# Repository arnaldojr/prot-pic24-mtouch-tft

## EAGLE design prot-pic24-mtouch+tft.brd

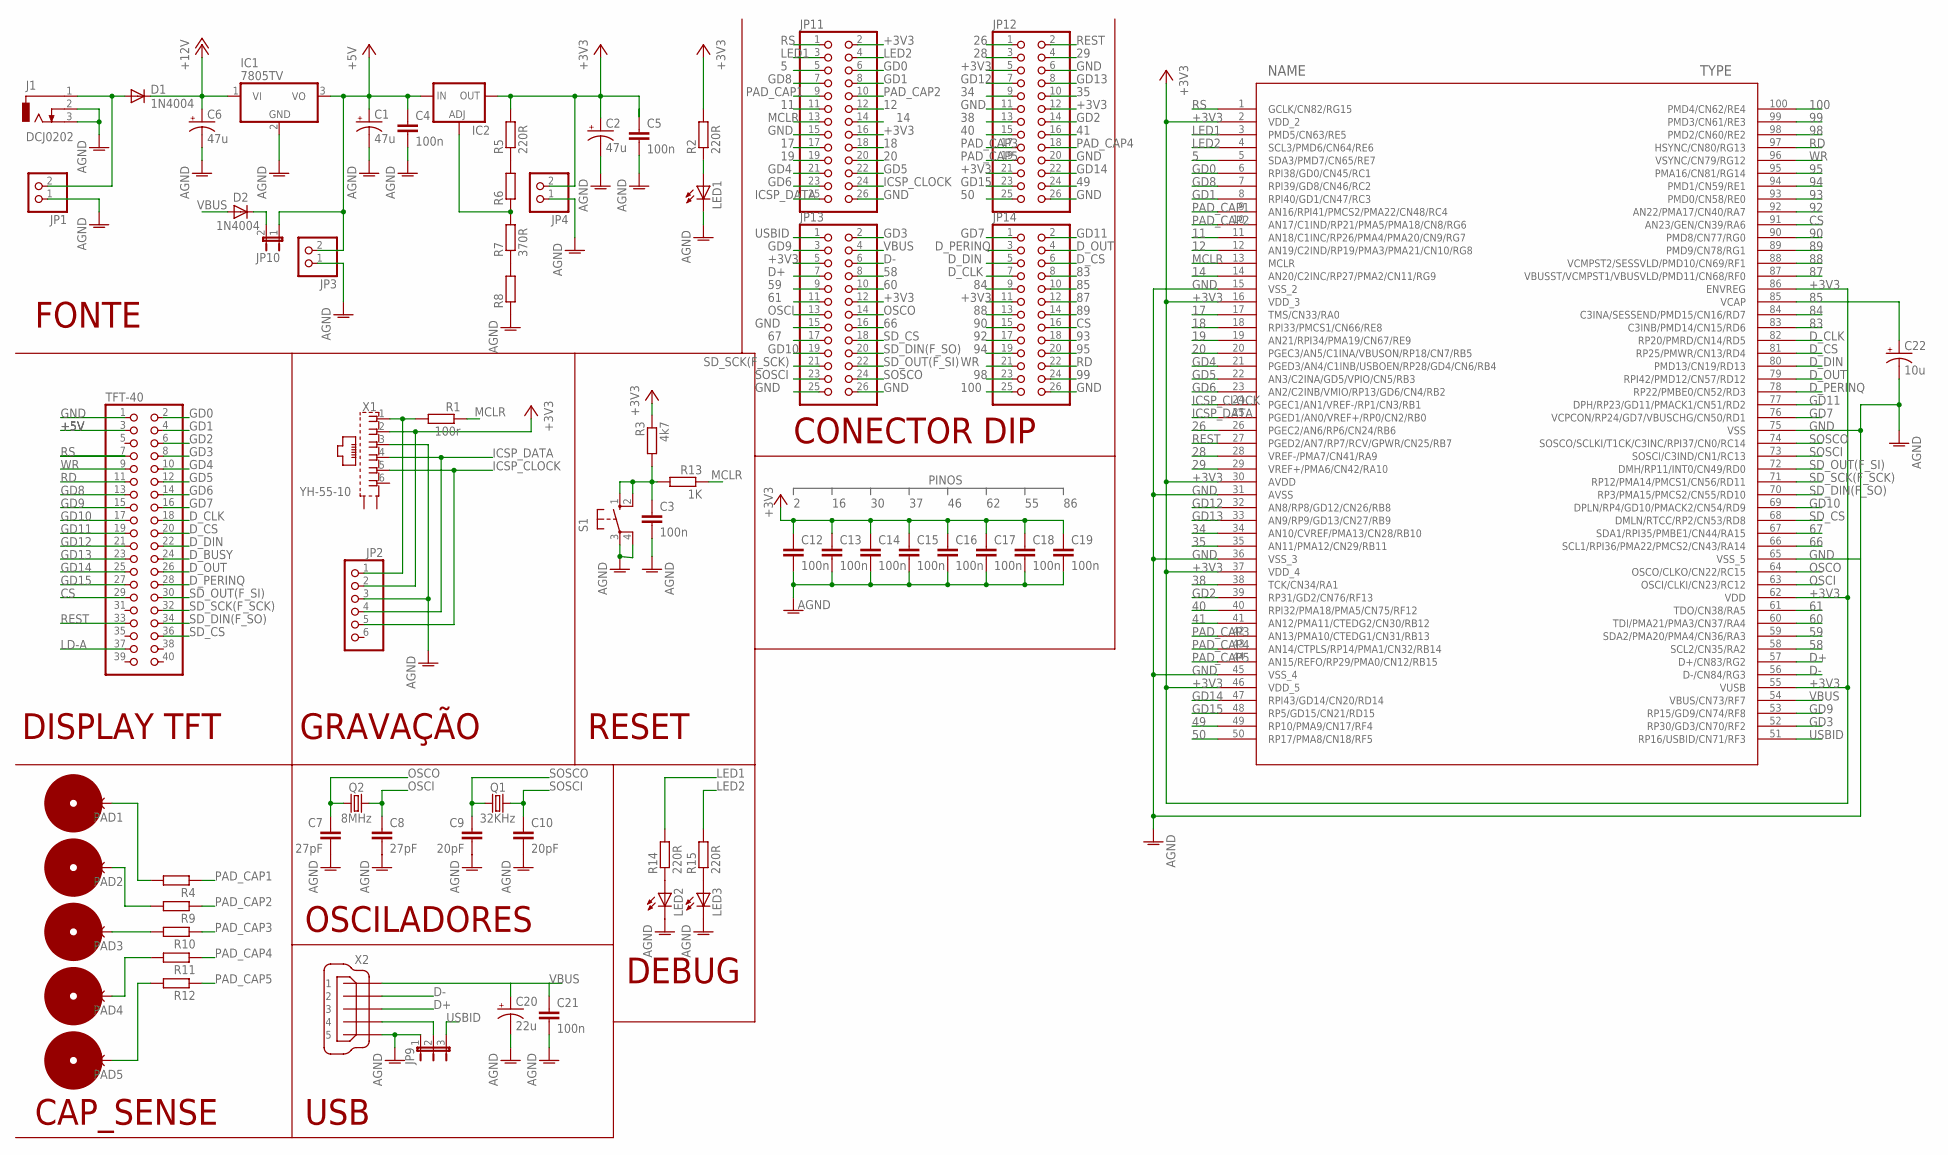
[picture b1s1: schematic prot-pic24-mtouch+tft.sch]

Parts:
C1, C2, C6: 47u; E2,5-5
C3, C4, C5: 100n; C050-025X075
C7, C8: 27pF; C025-030X050
C9, C10: 20pF; C025-030X050
C12: 100n; C025-025X050
C13, C14, C15, C16, C17, C18, C19, C21: 100n; C025-030X050
C20: 22u; E2,5-5
C22: 10u; E2,5-5
D1, D2: 1N4004; DO41-10
IC1: 7805TV; TO220V
IC2: LM317TS; 317TS
J1: DCJ0202
JP1, JP3, JP4: PINHD-1X2; 1X02
JP2: PINHD-1X6; 1X06
JP9: JP2E; JP2
JP10: JP1E; JP1
JP11, JP12, JP13, JP14: PINHD-2X13; 2X13
LED1, LED2, LED3: LED3MM
PAD1, PAD2, PAD3, PAD4, PAD5: SMD5; SMD2,54-5,08
Q1: 32KHz; TC26V
Q2: 8MHz; HC49/S
R1: 100r; 0204V
R2, R4, R5, R9, R10, R11, R12, R14, R15: 220R; 0204V
R3: 4k7; 0204V
R6, R8: R-EU_0204/2V; 0204V
R7: 370R; 0204V
R13: 1K; 0204V
S1: 10-XX; B3F-10XX
TFT-40: PINHD-2X20; 2X20
U$1: PIC24FJXXXDAX10_; TQFP100_12X12MC
X1: YH-55-10
X2: MINI-USB-32005-301; 32005-301

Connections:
5: JP11.5, U$1.5 (SDA3/PMD7/CN65/RE7)
11: JP11.11, U$1.11 (AN18/C1INC/RP26/PMA4/PMA20/CN9/RG7)
12: JP11.12, U$1.12 (AN19/C2IND/RP19/PMA3/PMA21/CN10/RG8)
14: JP11.14, U$1.14 (AN20/C2INC/RP27/PMA2/CN11/RG9)
17: JP11.17, U$1.17 (TMS/CN33/RA0)
18: JP11.18, U$1.18 (RPI33/PMCS1/CN66/RE8)
19: JP11.19, U$1.19 (AN21/RPI34/PMA19/CN67/RE9)
20: JP11.20, U$1.20 (PGEC3/AN5/C1INA/VBUSON/RP18/CN7/RB5)
26: JP12.1, U$1.26 (PGEC2/AN6/RP6/CN24/RB6)
28: JP12.3, U$1.28 (VREF-/PMA7/CN41/RA9)
29: JP12.4, U$1.29 (VREF+/PMA6/CN42/RA10)
34: JP12.9, U$1.34 (AN10/CVREF/PMA13/CN28/RB10)
35: JP12.10, U$1.35 (AN11/PMA12/CN29/RB11)
38: JP12.13, U$1.38 (TCK/CN34/RA1)
40: JP12.15, U$1.40 (RPI32/PMA18/PMA5/CN75/RF12)
41: JP12.16, U$1.41 (AN12/PMA11/CTEDG2/CN30/RB12)
49: JP12.24, U$1.49 (RP10/PMA9/CN17/RF4)
50: JP12.25, U$1.50 (RP17/PMA8/CN18/RF5)
58: JP13.8, U$1.58 (SCL2/CN35/RA2)
59: JP13.9, U$1.59 (SDA2/PMA20/PMA4/CN36/RA3)
60: JP13.10, U$1.60 (TDI/PMA21/PMA3/CN37/RA4)
61: JP13.11, U$1.61 (TDO/CN38/RA5)
66: JP13.16, U$1.66 (SCL1/RPI36/PMA22/PMCS2/CN43/RA14)
67: JP13.17, U$1.67 (SDA1/RPI35/PMBE1/CN44/RA15)
83: JP14.8, U$1.83 (C3INB/PMD14/CN15/RD6)
84: JP14.9, U$1.84 (C3INA/SESSEND/PMD15/CN16/RD7)
85: C22.+, JP14.10, U$1.85 (VCAP)
87: JP14.12, U$1.87 (VBUSST/VCMPST1/VBUSVLD/PMD11/CN68/RF0)
88: JP14.13, U$1.88 (VCMPST2/SESSVLD/PMD10/CN69/RF1)
89: JP14.14, U$1.89 (PMD9/CN78/RG1)
90: JP14.15, U$1.90 (PMD8/CN77/RG0)
92: JP14.17, U$1.92 (AN22/PMA17/CN40/RA7)
93: JP14.18, U$1.93 (PMD0/CN58/RE0)
94: JP14.19, U$1.94 (PMD1/CN59/RE1)
95: JP14.20, U$1.95 (PMA16/CN81/RG14)
98: JP14.23, U$1.98 (PMD2/CN60/RE2)
99: JP14.24, U$1.99 (PMD3/CN61/RE3)
100: JP14.25, U$1.100 (PMD4/CN62/RE4)
+3V3: C2.+, C5.1, C12.1, C13.1, C14.1, C15.1, C16.1, C17.1, C18.1, C19.1, IC2.2 (OUT), JP2.2, JP4.2, JP11.2, JP11.16, JP12.5, JP12.12, JP12.21, JP13.5, JP13.12, JP14.11, R2.2, R3.1, R5.2, U$1.2 (VDD_2), U$1.16 (VDD_3), U$1.30 (AVDD), U$1.37 (VDD_4), U$1.46 (VDD_5), U$1.55 (VUSB), U$1.62 (VDD), U$1.86 (ENVREG), X1.2
+5V: C1.+, C4.1, IC1.3 (VO), IC2.3 (IN), JP3.2, JP10.1, TFT-40.3
+12V: C6.+, D1.C, IC1.1 (VI)
AGND: LED2.K (C), LED3.K (C)
CS: JP14.16, TFT-40.29, U$1.91 (AN23/GEN/CN39/RA6)
D+: JP13.7, U$1.57 (D+/CN83/RG2), X2.3
D-: JP13.6, U$1.56 (D-/CN84/RG3), X2.2
D_BUSY: TFT-40.24
D_CLK: JP14.7, TFT-40.18, U$1.82 (RP20/PMRD/CN14/RD5)
D_CS: JP14.6, TFT-40.20, U$1.81 (RP25/PMWR/CN13/RD4)
D_DIN: JP14.5, TFT-40.22, U$1.80 (PMD13/CN19/RD13)
D_OUT: JP14.4, TFT-40.26, U$1.79 (RPI42/PMD12/CN57/RD12)
D_PERINQ: JP14.3, TFT-40.28, U$1.78 (RP22/PMBE0/CN52/RD3)
GD0: JP11.6, TFT-40.2, U$1.6 (RPI38/GD0/CN45/RC1)
GD1: JP11.8, TFT-40.4, U$1.8 (RPI40/GD1/CN47/RC3)
GD2: JP12.14, TFT-40.6, U$1.39 (RP31/GD2/CN76/RF13)
GD3: JP13.2, TFT-40.8, U$1.52 (RP30/GD3/CN70/RF2)
GD4: JP11.21, TFT-40.10, U$1.21 (PGED3/AN4/C1INB/USBOEN/RP28/GD4/CN6/RB4)
GD5: JP11.22, TFT-40.12, U$1.22 (AN3/C2INA/GD5/VPIO/CN5/RB3)
GD6: JP11.23, TFT-40.14, U$1.23 (AN2/C2INB/VMIO/RP13/GD6/CN4/RB2)
GD7: JP14.1, TFT-40.16, U$1.76 (VCPCON/RP24/GD7/VBUSCHG/CN50/RD1)
GD8: JP11.7, TFT-40.13, U$1.7 (RPI39/GD8/CN46/RC2)
GD9: JP13.3, TFT-40.15, U$1.53 (RP15/GD9/CN74/RF8)
GD10: JP13.19, TFT-40.17, U$1.69 (DPLN/RP4/GD10/PMACK2/CN54/RD9)
GD11: JP14.2, TFT-40.19, U$1.77 (DPH/RP23/GD11/PMACK1/CN51/RD2)
GD12: JP12.7, TFT-40.21, U$1.32 (AN8/RP8/GD12/CN26/RB8)
GD13: JP12.8, TFT-40.23, U$1.33 (AN9/RP9/GD13/CN27/RB9)
GD14: JP12.22, TFT-40.25, U$1.47 (RPI43/GD14/CN20/RD14)
GD15: JP12.23, TFT-40.27, U$1.48 (RP5/GD15/CN21/RD15)
GND: C1.-, C2.-, C3.2, C4.2, C5.2, C6.-, C7.2, C8.2, C9.2, C10.2, C12.2, C13.2, C14.2, C15.2, C16.2, C17.2, C18.2, C19.2, C20.-, C21.2, C22.-, IC1.2 (GND), J1.2, J1.3, JP1.1, JP2.3, JP3.1, JP4.1, JP9.1, JP11.15, JP11.26, JP12.6, JP12.11, JP12.20, JP12.26, JP13.15, JP13.25, JP13.26, JP14.26, LED1.K (C), R8.1, S1.3, S1.4 (P1), TFT-40.1, U$1.15 (VSS_2), U$1.31 (AVSS), U$1.36 (VSS_3), U$1.45 (VSS_4), U$1.65 (VSS_5), U$1.75 (VSS), X1.3, X2.5
ICSP_CLOCK: JP2.5, JP11.24, U$1.24 (PGEC1/AN1/VREF-/RP1/CN3/RB1), X1.5
ICSP_DATA: JP2.4, JP11.25, U$1.25 (PGED1/AN0/VREF+/RP0/CN2/RB0), X1.4
LD-A: TFT-40.37
LED1: JP11.3, R14.2, U$1.3 (PMD5/CN63/RE5)
LED2: JP11.4, R15.2, U$1.4 (SCL3/PMD6/CN64/RE6)
MCLR: JP11.13, R1.1, R13.1, U$1.13 (MCLR)
unnamed: D1.A, J1.1, JP1.2
unnamed: LED1.A, R2.1
unnamed: JP2.1, R1.2, X1.1
unnamed: R5.1, R6.2
unnamed: IC2.1 (ADJ), R6.1, R7.2
unnamed: R7.1, R8.2
unnamed: PAD1.1, R4.2
unnamed: JP9.2, X2.4
unnamed: PAD2.1, R9.2
unnamed: PAD3.1, R10.2
unnamed: PAD4.1, R11.2
unnamed: PAD5.1, R12.2
unnamed: C3.1, R3.2, R13.2, S1.1 (S), S1.2 (S1)
unnamed: LED2.A, R14.1
unnamed: D2.C, JP10.2
unnamed: LED3.A, R15.1
OSCI: C8.1, JP13.13, Q2.2, U$1.63 (OSCI/CLKI/CN23/RC12)
OSCO: C7.1, JP13.14, Q2.1, U$1.64 (OSCO/CLKO/CN22/RC15)
PAD_CAP1: JP11.9, R4.1, U$1.9 (AN16/RPI41/PMCS2/PMA22/CN48/RC4)
PAD_CAP2: JP11.10, R9.1, U$1.10 (AN17/C1IND/RP21/PMA5/PMA18/CN8/RG6)
PAD_CAP3: JP12.17, R10.1, U$1.42 (AN13/PMA10/CTEDG1/CN31/RB13)
PAD_CAP4: JP12.18, R11.1, U$1.43 (AN14/CTPLS/RP14/PMA1/CN32/RB14)
PAD_CAP5: JP12.19, R12.1, U$1.44 (AN15/REFO/RP29/PMA0/CN12/RB15)
RD: JP14.22, TFT-40.11, U$1.97 (HSYNC/CN80/RG13)
REST: JP12.2, TFT-40.33, U$1.27 (PGED2/AN7/RP7/RCV/GPWR/CN25/RB7)
RS: JP11.1, TFT-40.7, U$1.1 (GCLK/CN82/RG15)
SD_CS: JP13.18, TFT-40.36, U$1.68 (DMLN/RTCC/RP2/CN53/RD8)
SD_DIN(F_SO): JP13.20, TFT-40.34, U$1.70 (RP3/PMA15/PMCS2/CN55/RD10)
SD_OUT(F_SI): JP13.22, TFT-40.30, U$1.72 (DMH/RP11/INT0/CN49/RD0)
SD_SCK(F_SCK): JP13.21, TFT-40.32, U$1.71 (RP12/PMA14/PMCS1/CN56/RD11)
SOSCI: C10.1, JP13.23, Q1.2, U$1.73 (SOSCI/C3IND/CN1/RC13)
SOSCO: C9.1, JP13.24, Q1.1, U$1.74 (SOSCO/SCLKI/T1CK/C3INC/RPI37/CN0/RC14)
USBID: JP9.3, JP13.1, U$1.51 (RP16/USBID/CN71/RF3)
VBUS: C20.+, C21.1, D2.A, JP13.4, U$1.54 (VBUS/CN73/RF7), X2.1
WR: JP14.21, TFT-40.9, U$1.96 (VSYNC/CN79/RG12)

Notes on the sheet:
DISPLAY TFT
FONTE
GRAVAÇÃO
RESET
CAP_SENSE
OSCILADORES
CONECTOR DIP
PINOS
USB
DEBUG

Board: 2 copper layers, 66 parts (1 on the bottom side), 107 nets, no tracks yet.

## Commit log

2018-11-02 init commit
